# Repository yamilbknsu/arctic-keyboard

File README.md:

# ❄️ <span style="background: linear-gradient(rgb(33, 103, 243),rgb(18, 237, 252));-webkit-text-fill-color: transparent; -webkit-background-clip:text;">Arctic</span> - Split Keyboard

Repo structure:
- `ergogen` folder: [ergogen](https://github.com/ergogen/ergogen) config file and community footprints used
- `pcbs` folder: Finished KiCAD PCB files for left and right plates as well as SVG file used for designing the case
- `case` folder: `obj` file used to generate `.3MF` for 3D printed case.
- `config`, `build.yaml` and `zephyr`: [ZMK](https://zmk.dev/) firmware files for nice!nanov2 MCU

## Assembled Keyboard

## Materials
| Name                   | Qty | Reference                                                                              |
|------------------------|-----|----------------------------------------------------------------------------------------|
| PCB Plates             | 2   | One for each side                                                                      |
| 3D Printed case        | 1   | Four parts in total                                                                    |
| MX Switches            | 64  | From [Typeractive.xyz](https://typeractive.xyz/products/jwk-jwick-t1-tactile-switches) |
| MX Black Keycaps       | 52  | From [nuphy.com](https://nuphy.com/collections/keycaps/products/gem-msa)               |
| MX White Keycaps       | 12  | From [Amazon](https://www.amazon.com/dp/B0CBR6XFBY)                                    |
| nice!nano v2.0         | 2   | From [Typeractive.xyz](https://typeractive.xyz/products/nice-nano)                     |
| SMD Diodes             | 64  | From [Typeractive.xyz](https://typeractive.xyz/products/smd-diodes)                    |
| Kailh Hotswap Sockets  | 64  | From [Typeractive.xyz](https://typeractive.xyz/products/hotswap-sockets)               |
| Reset Button           | 2   | From [Typeractive.xyz](https://typeractive.xyz/products/reset-button)                  |
| Power Switch           | 2   | From [Typeractive.xyz](https://typeractive.xyz/products/power-switch)                  |
| Battery Jack           | 2   | From [Typeractive.xyz](https://typeractive.xyz/products/battery-jack)                  |
| Lithium Battery 750mAh | 2   | From [Typeractive.xyz](https://typeractive.xyz/products/lithium-battery-750mah)        |
| EZ-Solder Sockets (Opt)| 2   | From [Typeractive.xyz](https://typeractive.xyz/products/ez-machine-sockets-and-headers)|
| 2mm Rubber Feet (Opt)  | 10  | From [Typeractive.xyz](https://www.amazon.com/dp/B06XCNM69B)                           |
| EZ-Solder Sockets (Opt)| 2   | From [Typeractive.xyz](https://typeractive.xyz/products/ez-machine-sockets-and-headers)|
| M2 Screws and separator| 20  | 10 6mm M2 + 10 4mm M2 and 10 4mm M2 separators                                         |

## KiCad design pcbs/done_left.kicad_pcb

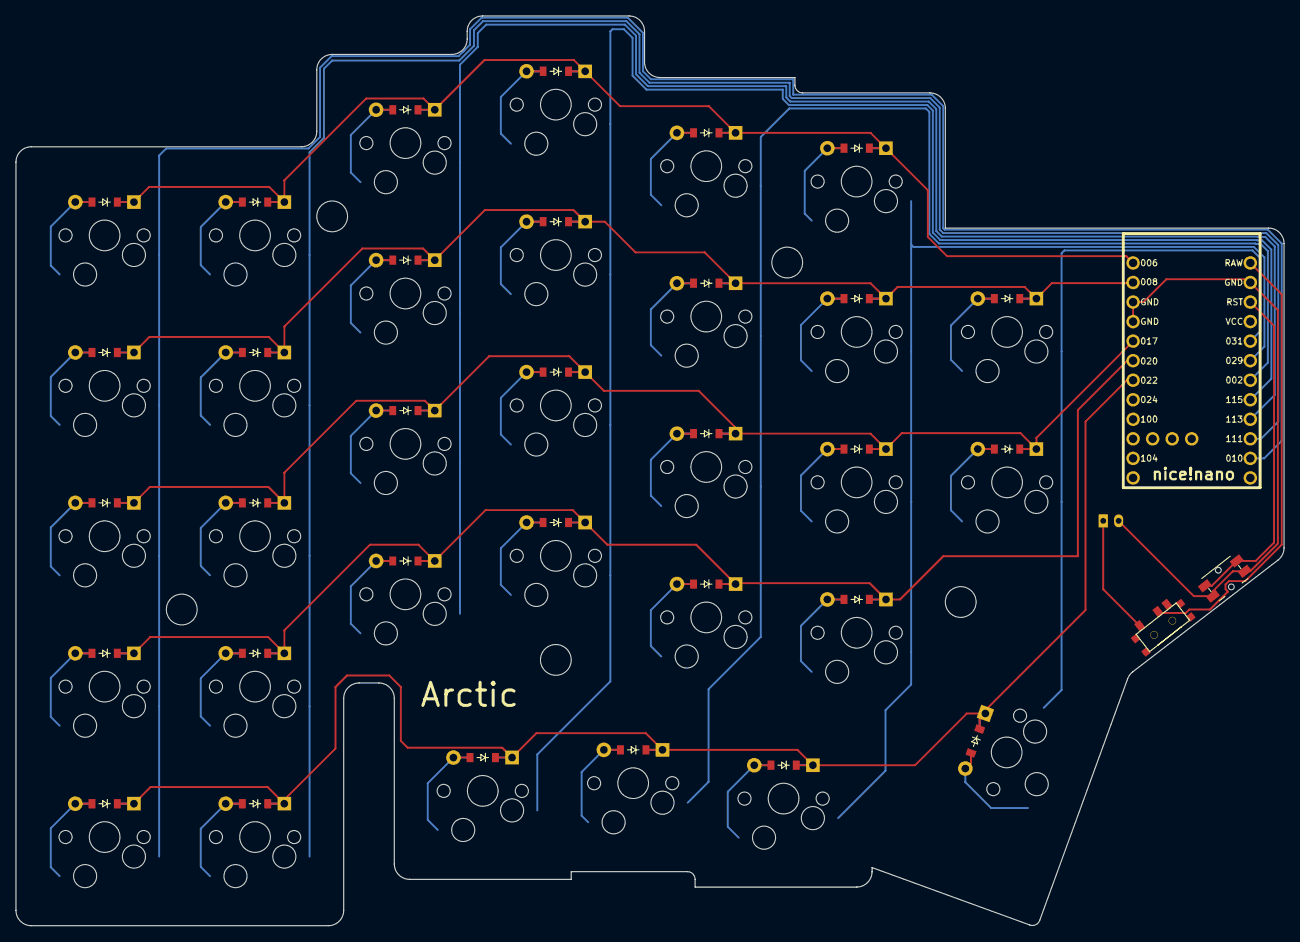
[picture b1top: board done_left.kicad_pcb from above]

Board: 2 copper layers, 164.8 x 118.2 mm, 68 parts (0 on the bottom side), 48 nets.

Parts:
B1: Panasonic_EVQPUL_EVQPUC
D1, D2, D3, D4, D5, D6, D7, D8, D9, D10, D11, D12, D13, D14, D15, D16, D17, D18, D19, D20, D21, D22, D23, D24, D25, D26, D27, D28, D29, D30, D31, D32: ComboDiode
JST1: JST_PH_S2B-PH-K_02x2.00mm_Angled
MCU1: nice_nano
S1, S2, S3, S4, S5, S6, S7, S8, S9, S10, S11, S12, S13, S14, S15, S16, S17, S18, S19, S20, S21, S22, S23, S24, S25, S26, S27, S28, S29, S30, S31, S32: MX
T1: SPDT_C128955

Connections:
GND: B1.1, JST1.2, MCU1.3, MCU1.4, MCU1.23
P002: MCU1.18, S19.1, S20.1, S21.1, S22.1, S30.1
P006: D5.1, D10.1, D14.1, D18.1, D22.1, D26.1, MCU1.1
P008: D4.1, D9.1, D13.1, D17.1, D21.1, D25.1, D28.1, MCU1.2
P010: MCU1.14, S1.1, S2.1, S3.1, S4.1, S5.1
P017: D3.1, D8.1, D12.1, D16.1, D20.1, D24.1, D27.1, MCU1.5
P020: D2.1, D7.1, D11.1, D15.1, D19.1, D23.1, MCU1.6
P022: D1.1, D6.1, D29.1, D30.1, D31.1, D32.1, MCU1.7
P029: MCU1.19, S23.1, S24.1, S25.1, S26.1, S31.1
P031: MCU1.20, S27.1, S28.1, S32.1
P111: MCU1.15, S6.1, S7.1, S8.1, S9.1, S10.1
P113: MCU1.16, S11.1, S12.1, S13.1, S14.1
P115: MCU1.17, S15.1, S16.1, S17.1, S18.1, S29.1
RAW: MCU1.24, T1.2
RST: B1.2, MCU1.22
actions_bottom: D2.2, S2.2
actions_home: D3.2, S3.2
actions_modifiers: D1.2, S1.2
actions_numbers: D5.2, S5.2
actions_top: D4.2, S4.2
back_thumb: D29.2, S29.2
forward_thumb: D32.2, S32.2
index_bottom: D19.2, S19.2
index_home: D20.2, S20.2
index_numbers: D22.2, S22.2
index_top: D21.2, S21.2
inner_bottom: D23.2, S23.2
inner_home: D24.2, S24.2
inner_numbers: D26.2, S26.2
inner_top: D25.2, S25.2
middle_bottom: D15.2, S15.2
middle_home: D16.2, S16.2
middle_numbers: D18.2, S18.2
middle_thumb: D30.2, S30.2
middle_top: D17.2, S17.2
pinky_bottom: D7.2, S7.2
pinky_home: D8.2, S8.2
pinky_modifiers: D6.2, S6.2
pinky_numbers: D10.2, S10.2
pinky_top: D9.2, S9.2
pos: JST1.1, T1.1
ring_bottom: D11.2, S11.2
ring_home: D12.2, S12.2
ring_numbers: D14.2, S14.2
ring_top: D13.2, S13.2
space_thumb: D31.2, S31.2
special_home: D27.2, S27.2
special_top: D28.2, S28.2

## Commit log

2025-02-02 Initial User Config.
2025-02-03 Incomplete keymap
2025-02-03 Fixed arctic.dtsi reference
2025-02-03 Added Keymap copy
2025-02-03 Updated Keymaps
2025-02-03 Fix keymap commands
2025-02-03 Added bluetooth commands
2025-02-03 Updates config
2025-02-03 Change name in Conf (oops)
2025-02-06 Fix left transform
2025-02-06 Updated left keymap
2025-02-06 Testing right keymaps
2025-02-07 Reset config
2025-02-07 Trying reset keymap
2025-02-07 Retry Reset
2025-02-07 Fix retry
2025-02-07 Reflash
2025-02-07 Another try of the config
2025-02-08 Try with minimal config file
2025-02-08 File name correction
2025-02-08 Append to last commit
2025-02-08 Initial keymap
2025-02-08 Fix keymap
2025-02-08 Changed arrrow map
2025-02-08 Revert "Changed arrrow map"
    This reverts commit d42a516d18e9dc47a0f41fab6a02644492d7584a.
2025-02-09 Added README
2025-02-09 Fix github actions
2025-02-09 Fix Zephyr dir
2025-02-09 Attempt to fix actions
2025-02-09 Github actions
2025-02-13 Try moving zephyr folder out
2025-02-13 Move zmk files out
2025-02-13 Fix BLSH keymap
2025-03-09 Updated Keymap and increased inactivity time
